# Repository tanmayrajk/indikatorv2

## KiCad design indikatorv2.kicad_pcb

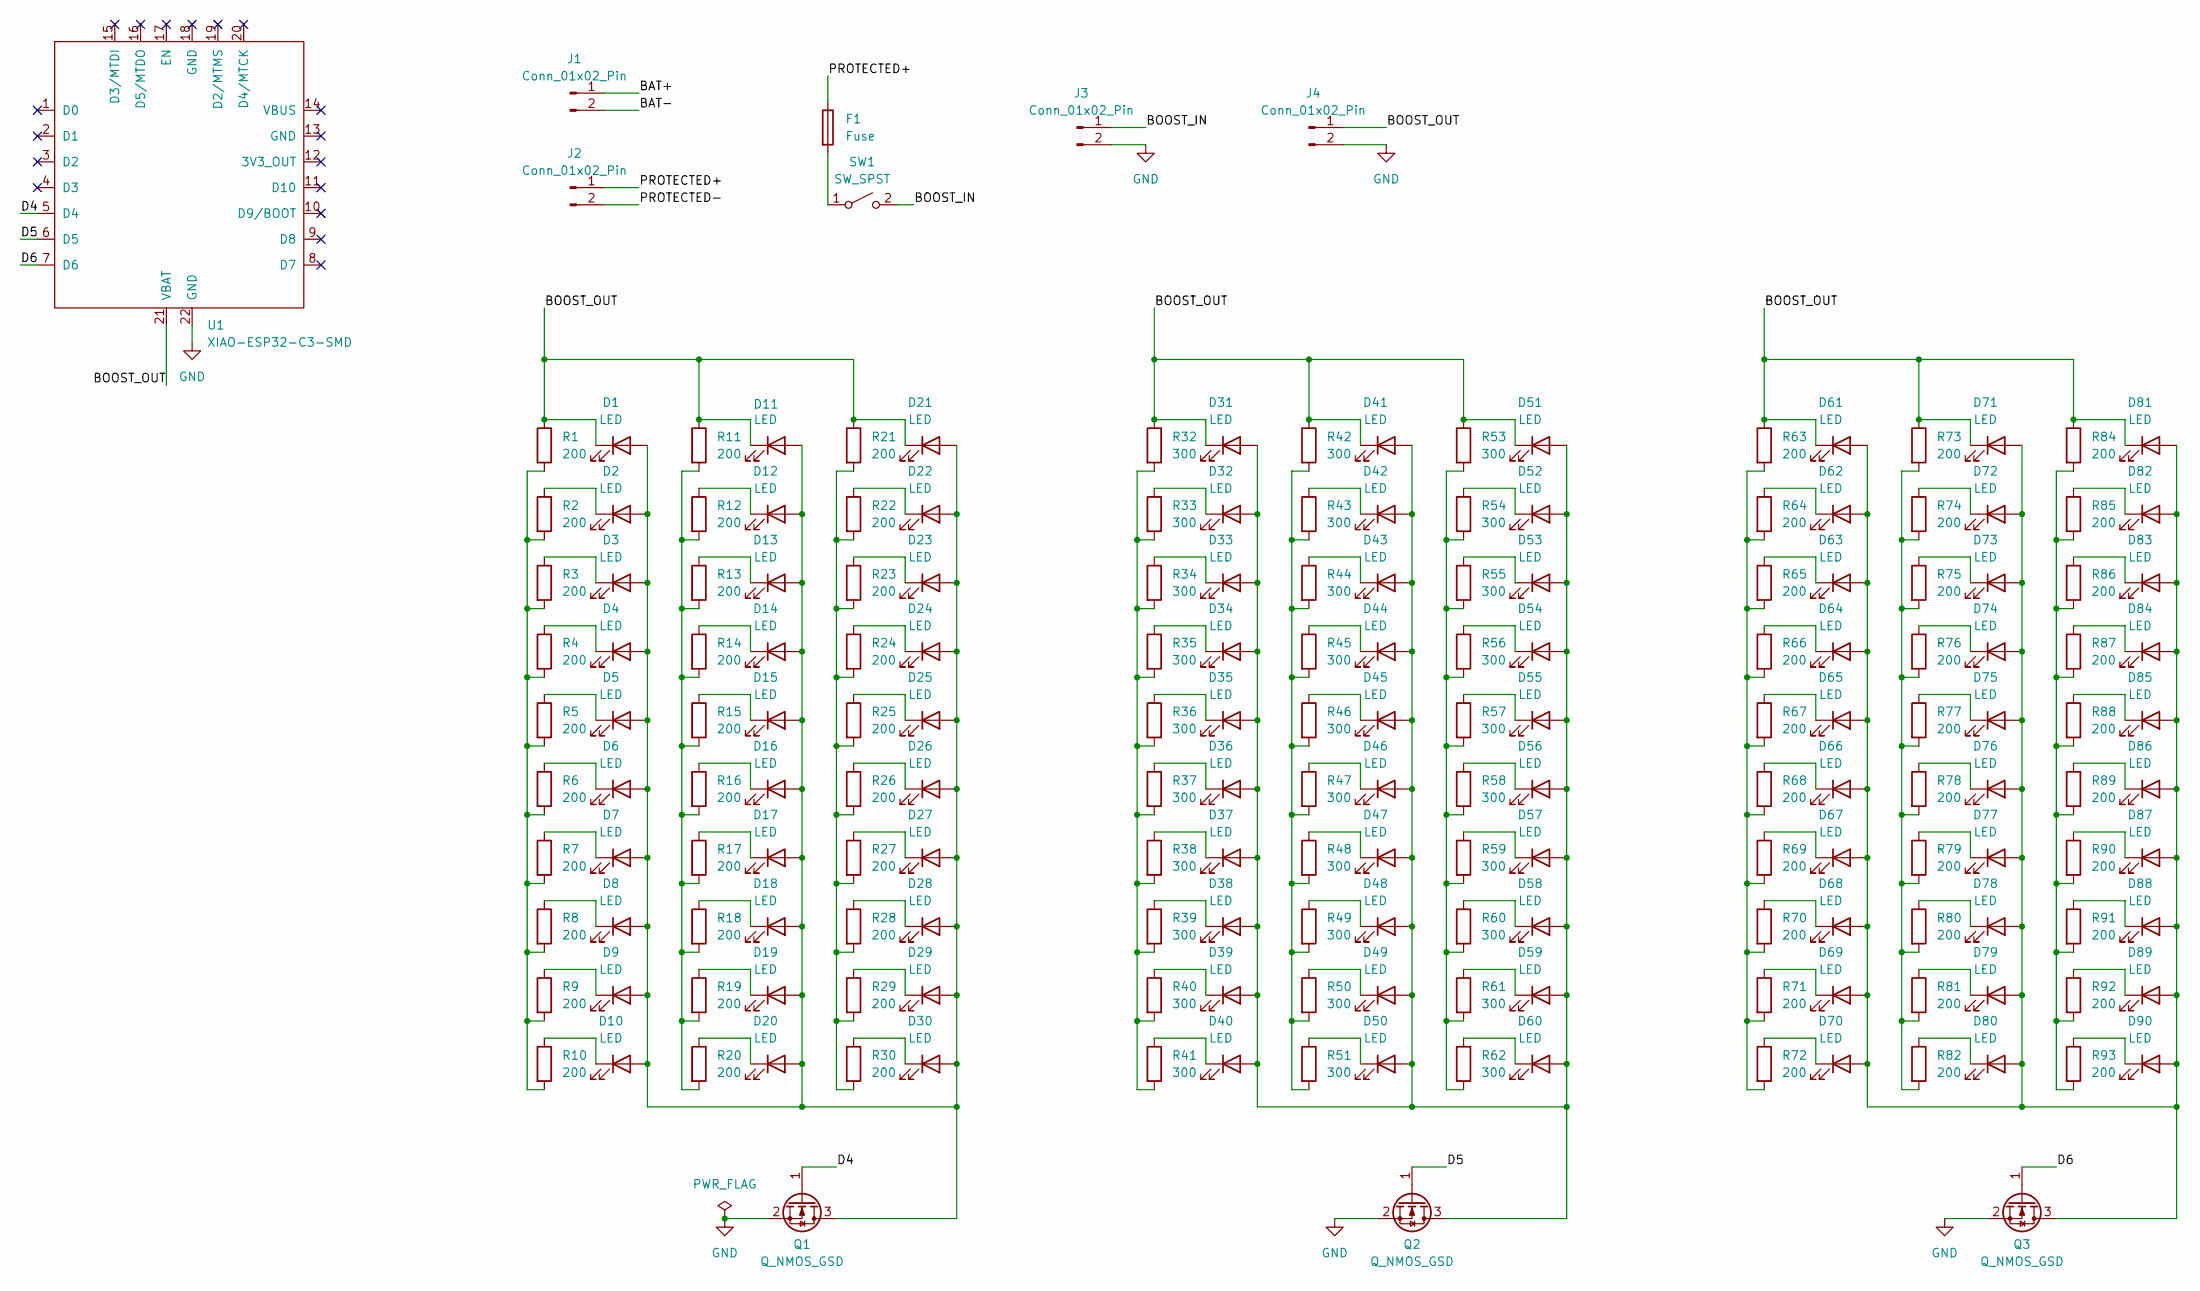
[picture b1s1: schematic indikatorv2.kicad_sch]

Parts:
D1, D2, D3, D4, D5, D6, D7, D8, D9, D10, D11, D12, D13, D14, D15, D16, D17, D18, D19, D20, D21, D22, D23, D24, D25, D26, D27, D28, D29, D30, D31, D32, D33, D34, D35, D36, D37, D38, D39, D40, D41, D42, D43, D44, D45, D46, D47, D48, D49, D50, D51, D52, D53, D54, D55, D56, D57, D58, D59, D60, D61, D62, D63, D64, D65, D66, D67, D68, D69, D70, D71, D72, D73, D74, D75, D76, D77, D78, D79, D80, D81, D82, D83, D84, D85, D86, D87, D88, D89, D90: LED; L128-CLR1003500000
F1: Fuse; FuseHolder_ELCOM_PBF-4
J1, J2, J3, J4: Conn_01x02_Pin; TerminalBlock_MaiXu_MX126-5.0-02P_1x02_P5.00mm
Q1, Q2, Q3: Q_NMOS_GSD; Converter_DCDC_XP_POWER-IAxxxxD_THT
R1, R2, R3, R4, R5, R6, R7, R8, R9, R10, R11, R12, R13, R14, R15, R16, R17, R18, R19, R20, R21, R22, R23, R24, R25, R26, R27, R28, R29, R30, R63, R64, R65, R66, R67, R68, R69, R70, R71, R72, R73, R74, R75, R76, R77, R78, R79, R80, R81, R82, R84, R85, R86, R87, R88, R89, R90, R91, R92, R93: 200; R_0805_2012Metric
R32, R33, R34, R35, R36, R37, R38, R39, R40, R41, R42, R43, R44, R45, R46, R47, R48, R49, R50, R51, R53, R54, R55, R56, R57, R58, R59, R60, R61, R62: 300; R_0805_2012Metric
SW1: SW_SPST; SW_NKK_GW12LJP
U1: XIAO-ESP32-C3-SMD; MCU_Seeed_ESP32C3

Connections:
/BAT+: J1.1
/BAT-: J1.2
/BOOST_IN: J3.1, SW1.2 (B)
/BOOST_OUT: D1.1 (K), D11.1 (K), D21.1 (K), D31.1 (K), D41.1 (K), D51.1 (K), D61.1 (K), D71.1 (K), D81.1 (K), J4.1, R1.1, R11.1, R21.1, R32.1, R42.1, R53.1, R63.1, R73.1, R84.1, U1.21 (VBAT)
/D4: Q1.1 (G), U1.5 (D4)
/D5: Q2.1 (G), U1.6 (D5)
/D6: Q3.1 (G), U1.7 (D6)
/PROTECTED+: F1.1, J2.1
/PROTECTED-: J2.2
GND: J3.2, J4.2, Q1.2 (S), Q2.2 (S), Q3.2 (S), U1.22 (GND)
unnamed: D1.2 (A), D2.2 (A), D3.2 (A), D4.2 (A), D5.2 (A), D6.2 (A), D7.2 (A), D8.2 (A), D9.2 (A), D10.2 (A), D11.2 (A), D12.2 (A), D13.2 (A), D14.2 (A), D15.2 (A), D16.2 (A), D17.2 (A), D18.2 (A), D19.2 (A), D20.2 (A), D21.2 (A), D22.2 (A), D23.2 (A), D24.2 (A), D25.2 (A), D26.2 (A), D27.2 (A), D28.2 (A), D29.2 (A), D30.2 (A), Q1.3 (D)
unnamed: D2.1 (K), R2.1
unnamed: D3.1 (K), R3.1
unnamed: D4.1 (K), R4.1
unnamed: D5.1 (K), R5.1
unnamed: D6.1 (K), R6.1
unnamed: D7.1 (K), R7.1
unnamed: D8.1 (K), R8.1
unnamed: D9.1 (K), R9.1
unnamed: D10.1 (K), R10.1
unnamed: D12.1 (K), R12.1
unnamed: D13.1 (K), R13.1
unnamed: D14.1 (K), R14.1
unnamed: D15.1 (K), R15.1
unnamed: D16.1 (K), R16.1
unnamed: D17.1 (K), R17.1
unnamed: D18.1 (K), R18.1
unnamed: D19.1 (K), R19.1
unnamed: D20.1 (K), R20.1
unnamed: D22.1 (K), R22.1
unnamed: D23.1 (K), R23.1
unnamed: D24.1 (K), R24.1
unnamed: D25.1 (K), R25.1
unnamed: D26.1 (K), R26.1
unnamed: D27.1 (K), R27.1
unnamed: D28.1 (K), R28.1
unnamed: D29.1 (K), R29.1
unnamed: D30.1 (K), R30.1
unnamed: D31.2 (A), D32.2 (A), D33.2 (A), D34.2 (A), D35.2 (A), D36.2 (A), D37.2 (A), D38.2 (A), D39.2 (A), D40.2 (A), D41.2 (A), D42.2 (A), D43.2 (A), D44.2 (A), D45.2 (A), D46.2 (A), D47.2 (A), D48.2 (A), D49.2 (A), D50.2 (A), D51.2 (A), D52.2 (A), D53.2 (A), D54.2 (A), D55.2 (A), D56.2 (A), D57.2 (A), D58.2 (A), D59.2 (A), D60.2 (A), Q2.3 (D)
unnamed: D32.1 (K), R33.1
unnamed: D33.1 (K), R34.1
unnamed: D34.1 (K), R35.1
unnamed: D35.1 (K), R36.1
unnamed: D36.1 (K), R37.1
unnamed: D37.1 (K), R38.1
unnamed: D38.1 (K), R39.1
unnamed: D39.1 (K), R40.1
unnamed: D40.1 (K), R41.1
unnamed: D42.1 (K), R43.1
unnamed: D43.1 (K), R44.1
unnamed: D44.1 (K), R45.1
unnamed: D45.1 (K), R46.1
unnamed: D46.1 (K), R47.1
unnamed: D47.1 (K), R48.1
unnamed: D48.1 (K), R49.1
unnamed: D49.1 (K), R50.1
unnamed: D50.1 (K), R51.1
unnamed: D52.1 (K), R54.1
unnamed: D53.1 (K), R55.1
unnamed: D54.1 (K), R56.1
unnamed: D55.1 (K), R57.1
unnamed: D56.1 (K), R58.1
unnamed: D57.1 (K), R59.1
unnamed: D58.1 (K), R60.1
unnamed: D59.1 (K), R61.1
unnamed: D60.1 (K), R62.1
unnamed: D61.2 (A), D62.2 (A), D63.2 (A), D64.2 (A), D65.2 (A), D66.2 (A), D67.2 (A), D68.2 (A), D69.2 (A), D70.2 (A), D71.2 (A), D72.2 (A), D73.2 (A), D74.2 (A), D75.2 (A), D76.2 (A), D77.2 (A), D78.2 (A), D79.2 (A), D80.2 (A), D81.2 (A), D82.2 (A), D83.2 (A), D84.2 (A), D85.2 (A), D86.2 (A), D87.2 (A), D88.2 (A), D89.2 (A), D90.2 (A), Q3.3 (D)
unnamed: D62.1 (K), R64.1
unnamed: D63.1 (K), R65.1
unnamed: D64.1 (K), R66.1
unnamed: D65.1 (K), R67.1
unnamed: D66.1 (K), R68.1
unnamed: D67.1 (K), R69.1
unnamed: D68.1 (K), R70.1
unnamed: D69.1 (K), R71.1
unnamed: D70.1 (K), R72.1
unnamed: D72.1 (K), R74.1
unnamed: D73.1 (K), R75.1
unnamed: D74.1 (K), R76.1
unnamed: D75.1 (K), R77.1
unnamed: D76.1 (K), R78.1
unnamed: D77.1 (K), R79.1
unnamed: D78.1 (K), R80.1
unnamed: D79.1 (K), R81.1
unnamed: D80.1 (K), R82.1
unnamed: D82.1 (K), R85.1
unnamed: D83.1 (K), R86.1
unnamed: D84.1 (K), R87.1
unnamed: D85.1 (K), R88.1
unnamed: D86.1 (K), R89.1
unnamed: D87.1 (K), R90.1
unnamed: D88.1 (K), R91.1
unnamed: D89.1 (K), R92.1
unnamed: D90.1 (K), R93.1
unnamed: R1.2, R2.2, R3.2, R4.2, R5.2, R6.2, R7.2, R8.2, R9.2, R10.2
unnamed: R11.2, R12.2, R13.2, R14.2, R15.2, R16.2, R17.2, R18.2, R19.2, R20.2
unnamed: R21.2, R22.2, R23.2, R24.2, R25.2, R26.2, R27.2, R28.2, R29.2, R30.2
unnamed: R32.2, R33.2, R34.2, R35.2, R36.2, R37.2, R38.2, R39.2, R40.2, R41.2
unnamed: R42.2, R43.2, R44.2, R45.2, R46.2, R47.2, R48.2, R49.2, R50.2, R51.2
unnamed: R53.2, R54.2, R55.2, R56.2, R57.2, R58.2, R59.2, R60.2, R61.2, R62.2
unnamed: R63.2, R64.2, R65.2, R66.2, R67.2, R68.2, R69.2, R70.2, R71.2, R72.2
unnamed: R73.2, R74.2, R75.2, R76.2, R77.2, R78.2, R79.2, R80.2, R81.2, R82.2
unnamed: R84.2, R85.2, R86.2, R87.2, R88.2, R89.2, R90.2, R91.2, R92.2, R93.2
unnamed: F1.2, SW1.1 (A)

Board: 2 copper layers, 190 parts (0 on the bottom side), 101 nets, no tracks yet.
